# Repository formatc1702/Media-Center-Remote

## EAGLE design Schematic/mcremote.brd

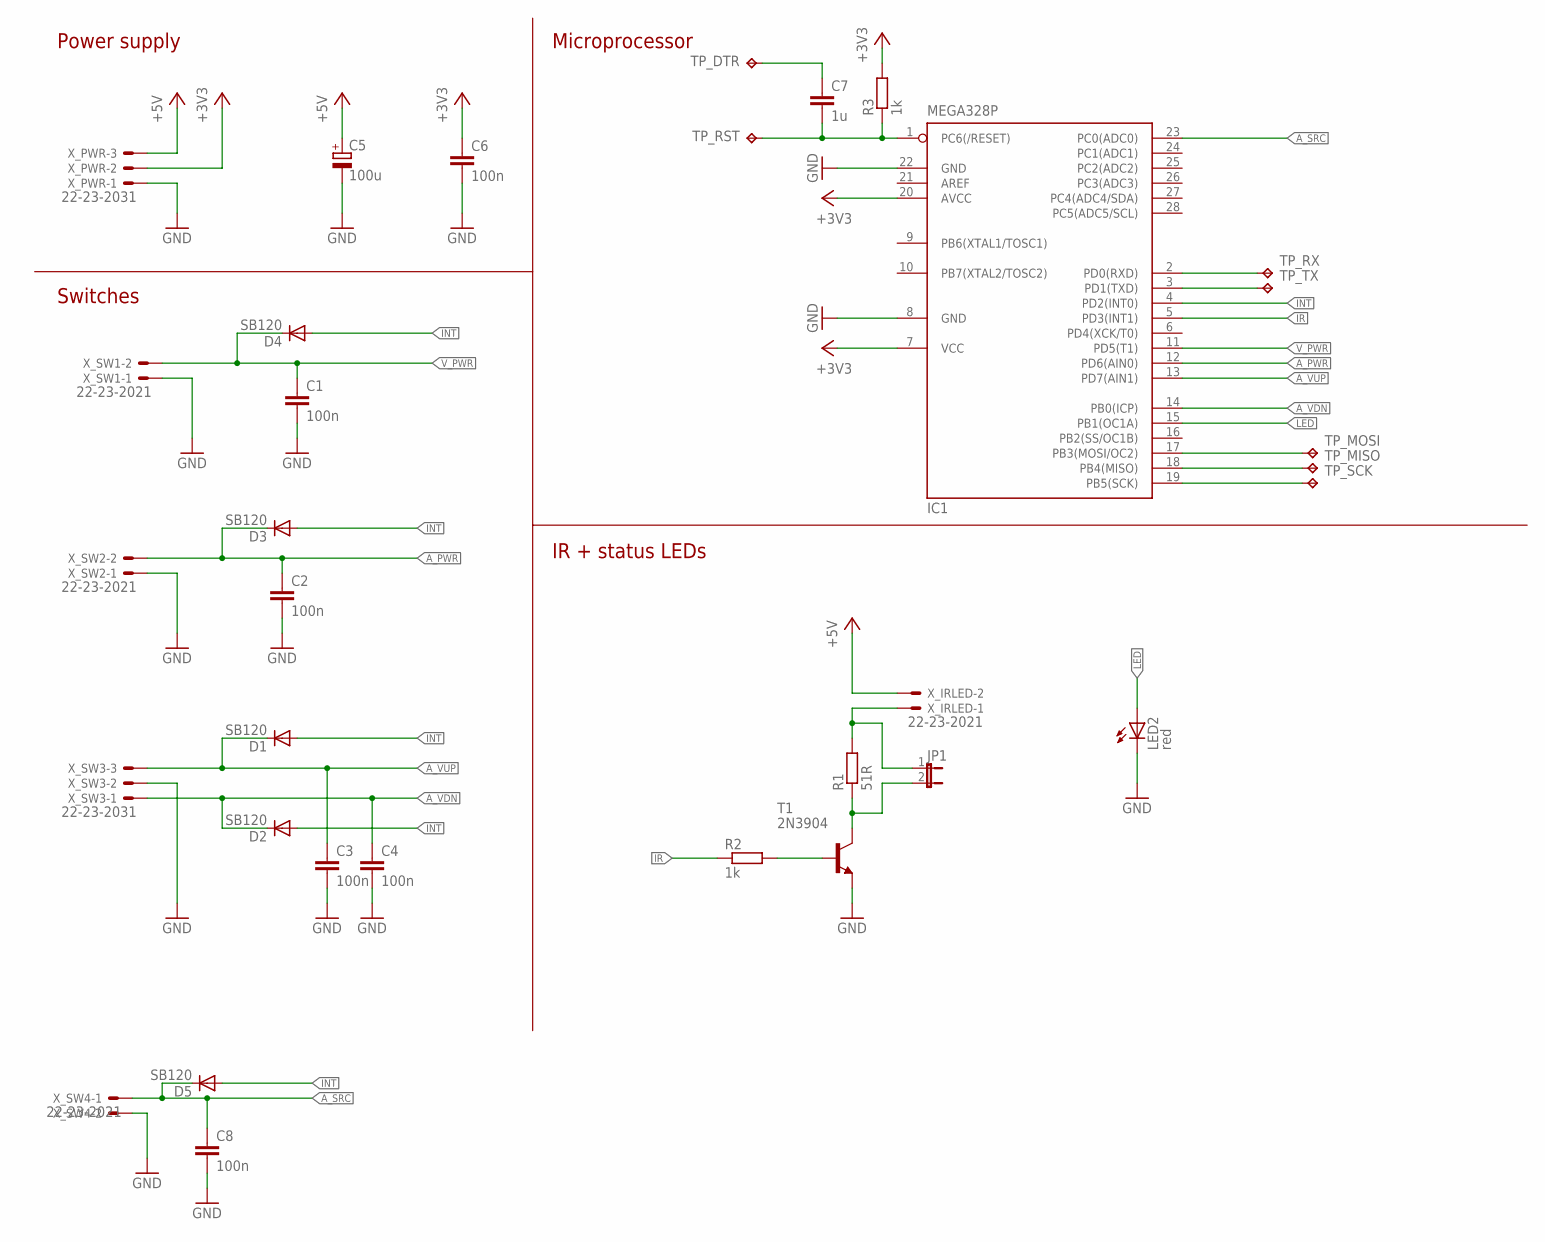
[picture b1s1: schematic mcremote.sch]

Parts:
C1, C2, C3, C4, C6, C8: 100n; C025-024X044
C5: 100u; E3,5-8
C7: 1u; C025-024X044
D1, D2, D3, D4: SB120; DO41-10
D5: SB120; DO41-7.6
IC1: MEGA328P; DIL28-3
JP1: JP1E; JP1
LED2: red; LED3MM
R1: 51R; 0207/7
R2, R3: 1k; 0207/7
T1: 2N3904; TO92
TP_DTR: TPPAD1-13; P1-13
TP_MISO: TPPAD1-13; P1-13
TP_MOSI: TPPAD1-13; P1-13
TP_RST: TPPAD1-13; P1-13
TP_RX: TPPAD1-13; P1-13
TP_SCK: TPPAD1-13; P1-13
TP_TX: TPPAD1-13; P1-13
X_IRLED: 22-23-2021
X_PWR: 22-23-2031
X_SW1, X_SW2, X_SW4: 22-23-2021
X_SW3: 22-23-2031

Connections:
+3V3: C6.1, IC1.7 (VCC), IC1.20 (AVCC), R3.2, X_PWR.2
+6V: C5.+, X_IRLED.2, X_PWR.3
A_PWR: C2.1, D3.C, IC1.12 (PD6(AIN0)), X_SW2.2
A_SRC: C8.1, D5.C, IC1.23 (PC0(ADC0)), X_SW4.1
A_VDN: C4.1, D2.C, IC1.14 (PB0(ICP)), X_SW3.1
A_VUP: C3.1, D1.C, IC1.13 (PD7(AIN1)), X_SW3.3
GND: C1.2, C2.2, C3.2, C4.2, C5.-, C6.2, C8.2, IC1.8 (GND), IC1.22 (GND), LED2.K (C), T1.3 (E), X_PWR.1, X_SW1.1, X_SW2.1, X_SW3.2, X_SW4.2
INT: D1.A, D2.A, D3.A, D4.A, D5.A, IC1.4 (PD2(INT0))
IR: IC1.5 (PD3(INT1)), R2.1
LED: IC1.15 (PB1(OC1A)), LED2.A
MISO: IC1.18 (PB4(MISO)), TP_MISO.TP
MOSI: IC1.17 (PB3(MOSI/OC2)), TP_MOSI.TP
unnamed: JP1.1, R1.2, X_IRLED.1
unnamed: JP1.2, R1.1, T1.1 (C)
unnamed: R2.2, T1.2 (B)
unnamed: C7.2, IC1.1 (PC6(/RESET)), R3.1, TP_RST.TP
unnamed: C7.1, TP_DTR.TP
RX: IC1.2 (PD0(RXD)), TP_RX.TP
SCK: IC1.19 (PB5(SCK)), TP_SCK.TP
TX: IC1.3 (PD1(TXD)), TP_TX.TP
V_PWR: C1.1, D4.C, IC1.11 (PD5(T1)), X_SW1.2

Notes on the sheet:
Power supply
Switches
Microprocessor
IR + status LEDs

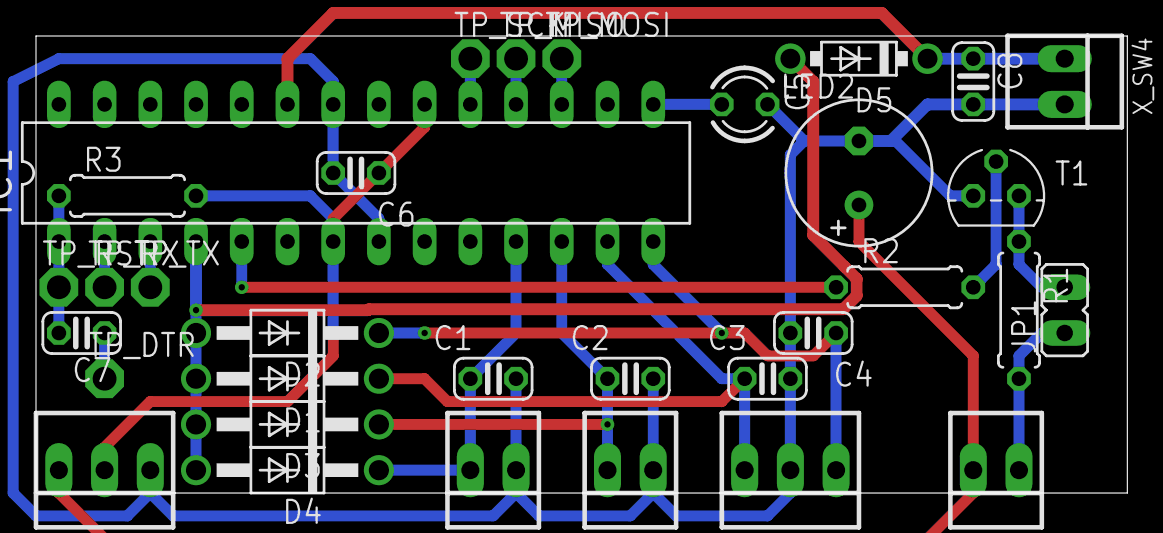
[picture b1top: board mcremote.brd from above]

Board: 2 copper layers, 60.6 x 25.4 mm, 33 parts (0 on the bottom side), 21 nets.

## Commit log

2019-07-14 Initial Arduino Project with IRemote library
2019-07-14 Record required remote codes
2019-07-14 First working demo for Onkyo Stereo
2019-07-14 Working demo for BenQ projector too
2019-07-14 Revert "Working demo for BenQ projector too"
    This reverts commit d0dc442eba0bf6380bc7d5ecb4ff7ad0d7fe5f36.
2019-07-14 Vol up/down demo
2019-07-15 Add documentation on NEC IR protocol
2019-07-15 Vol Up/Down only
2019-07-15 Remove redundant documentation
2019-08-09 Simple sleep test with IR
2019-08-09 Four buttons + sleep working
2019-08-29 Change UC CPU speed
    Using old Arduino Pro Mini with internal 8 MHz oscillator now
2019-09-28 Use RocketScream Low-Power library
2019-11-24 Add PCB design, adjust pins in firmware
2020-01-17 Add audio source select button to schematic + PCB
2020-01-17 Add audio source select button in firmware
2020-01-17 Rearrange schematic
2020-05-11 Add schematic PDF
2020-05-11 Add mechanical drawing
2020-05-11 Add photos
